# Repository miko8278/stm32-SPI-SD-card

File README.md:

# stm32-SPI-SD-card

This project was developed as part of a Bachelor's thesis for the [BHT Berlin](https://www.bht-berlin.de/) and makes use of the following open-source filesystem implementations:

## FatFs

This project uses **FatFs** by ChaN.

- Project: [FatFs – Official Website](https://elm-chan.org/fsw/ff/00index_e.html)
- The LittleFS source code used by this project is included in this repository under `code/spi-sdcardwrite/FatFs`.

## LittleFS

This project also uses **littlefs** by the littlefs-project.

- Project: [LittleFS – GitHub Repository](https://github.com/littlefs-project/littlefs)
- The littlefs source code used by this project is included in this repository under `code/spi-sdcardwrite/littlefs`.

## Project

The purpose of this project is to investigate and compare filesystem implementations for SD cards operated in SPI mode, using an **STM32G431** microcontroller.

The project is written in **C++20** and developed using **VS Codium**, **Cortex-Debug**, and the **GNU Arm Embedded Toolchain**.

The filesystem implementations are third-party software and are subject to their respective licenses. Please refer to the corresponding license files for the complete license terms.

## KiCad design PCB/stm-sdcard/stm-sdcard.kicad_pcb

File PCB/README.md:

# PCB Page

For this project [KiCAD 10.0](https://www.kicad.org/) was used.

## Used Parts

[ST STM32G431CBT6] https://www.lcsc.com/product-detail/C529355.html
[SD-Card Slot] https://www.lcsc.com/product-detail/C19189036.html
[USB Type-C connector] https://www.lcsc.com/product-detail/C668624.html
[LDO TI] https://www.lcsc.com/product-detail/C15578.html

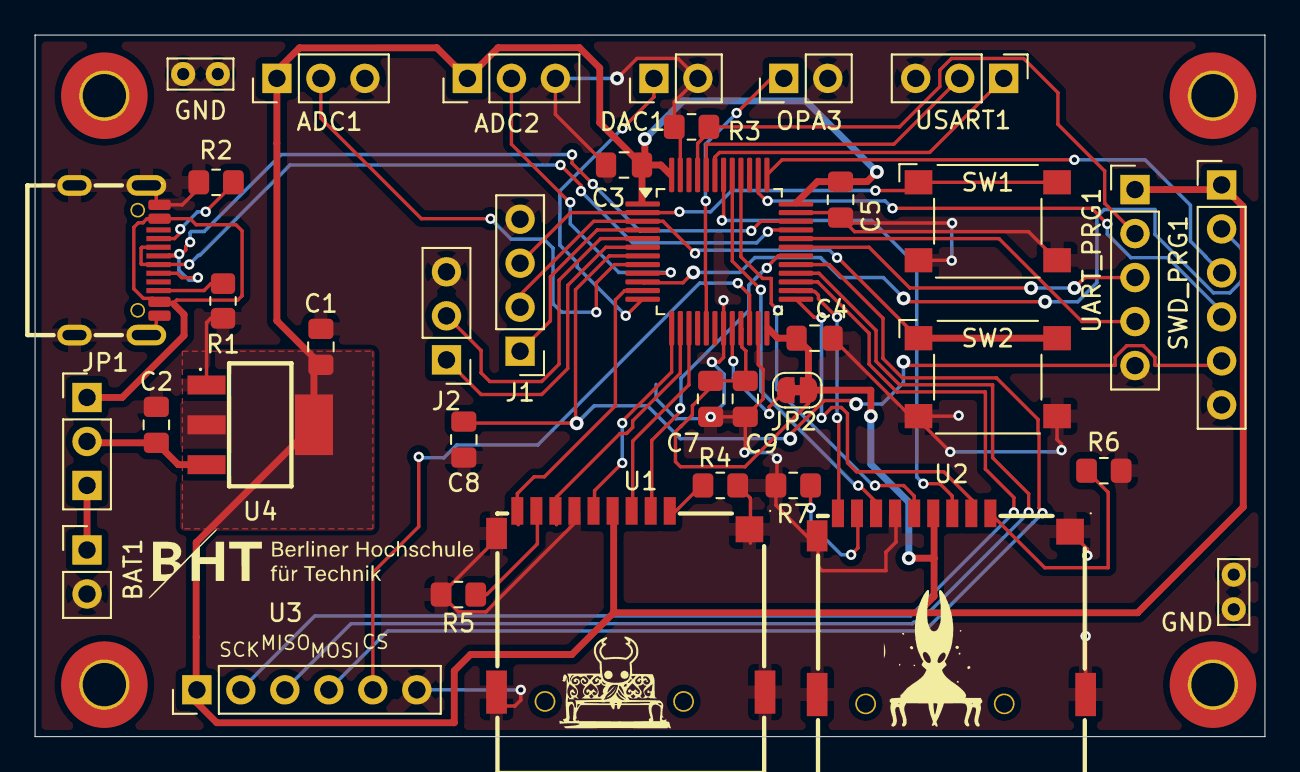
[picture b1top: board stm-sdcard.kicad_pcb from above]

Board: 2 copper layers, 71.0 x 40.5 mm, 37 parts (0 on the bottom side), 46 nets.

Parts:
ADC1, ADC2: Conn_01x03_Pin; PinHeader_1x03_P2.54mm_Vertical
BAT1: Conn_01x02_Pin; PinHeader_1x02_P2.54mm_Vertical
C1: 2.2uF; C_0805_2012Metric_Pad1.18x1.45mm_HandSolder
C2, C9: 1uF; C_0805_2012Metric_Pad1.18x1.45mm_HandSolder
C3, C4, C5, C7, C8: 100nF; C_0805_2012Metric_Pad1.18x1.45mm_HandSolder
DAC1: Conn_01x02_Pin; PinHeader_1x02_P2.54mm_Vertical
GND: TestPoint_Bridge_Pitch2.0mm_Drill0.7mm
GND#2: TestPoint_Bridge_Pitch2.0mm_Drill0.7mm
J1: Conn_01x04_Pin; PinHeader_1x04_P2.54mm_Vertical
J2: Conn_01x03_Pin; PinHeader_1x03_P2.54mm_Vertical
JP1: Jumper_3_Open; PinHeader_1x03_P2.54mm_Vertical
JP2: SolderJumper_2_Bridged; SolderJumper-2_P1.3mm_Bridged_RoundedPad1.0x1.5mm
OPA3: Conn_01x02_Pin; PinHeader_1x02_P2.54mm_Vertical
R1, R2: 5k1; R_0805_2012Metric_Pad1.20x1.40mm_HandSolder
R3: 20K; R_0805_2012Metric_Pad1.20x1.40mm_HandSolder
R4, R5, R6, R7: 50k; R_0805_2012Metric_Pad1.20x1.40mm_HandSolder
STM1: STM32G431CBTx; LQFP-48_7x7mm_P0.5mm
SW1, SW2: SW_Push; SW_SPST_Omron_B3FS-105xP
SWD_PRG1: Conn_01x06_Pin; PinHeader_1x06_P2.54mm_Vertical
U1, U2: HX TF-CARD H1.8; TF-SMD_HX-TF-CARD-H1.8-SY
U3: Conn_01x06_Pin; PinHeader_1x06_P2.54mm_Vertical
U4: TLV1117LV33DCYR; SOT-223_L6.7-W3.5-P2.30-BR
UART_PRG1: Conn_01x05_Pin; PinHeader_1x05_P2.54mm_Vertical
USART1: Conn_01x03_Pin; PinHeader_1x03_P2.54mm_Vertical
USB1: TYPE-C 16P; USB-C-SMD_TYPE-C16PIN_C668624

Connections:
+3.3V: ADC1.1, ADC2.1, C1.1, C3.1, C4.1, C5.1, C7.1, C9.1, JP2.1 (A), STM1.1 (VBAT), STM1.21 (VDDA), STM1.24 (VDD), STM1.36 (VDD), STM1.48 (VDD), SWD_PRG1.1, U1.4 (VDD), U2.4 (VDD), U3.1, U4.2 (OUT), U4.4 (OUT), UART_PRG1.1
+5V: C2.1, JP1.2 (C), U4.3 (IN)
/PA0_ADC1: ADC1.2, STM1.8 (PA0)
/PA1_ADC2: ADC2.2, STM1.9 (PA1)
/PA2_VCP_Tx: STM1.10 (PA2), SWD_PRG1.2
/PA3: STM1.11 (PA3), U1.9 (CD)
/PA4_DAC1: DAC1.1, STM1.12 (PA4)
/PA5: STM1.13 (PA5), U1.5 (CLK)
/PA6: STM1.14 (PA6), U1.7 (DAT0)
/PA7: STM1.15 (PA7), U1.3 (CMD)
/PA8: STM1.30 (PA8), U1.2 (CD/DAT3)
/PA9_Tx_BOOT: STM1.31 (PA9), UART_PRG1.3
/PA10_Rx_BOOT: STM1.32 (PA10), UART_PRG1.4
/PA13_SWDIO: STM1.37 (PA13), SWD_PRG1.3
/PA14_SWDCLK: STM1.38 (PA14), SWD_PRG1.4
/PB1_OPAMP3_OUT: OPA3.1, STM1.17 (PB1)
/PB3: STM1.40 (PB3), U2.5 (CLK)
/PB4: STM1.41 (PB4), U2.7 (DAT0)
/PB5: STM1.42 (PB5), U2.3 (CMD)
/PB6_USART1_RX: STM1.44 (PB7), USART1.2
/PB6_USART1_TX: STM1.43 (PB6), USART1.1
/PB8_BOOT0: R3.2, STM1.45 (PB8), UART_PRG1.2
/PB10: STM1.22 (PB10), U3.5
/PB11: STM1.25 (PB11), U2.2 (CD/DAT3)
/PB12: STM1.26 (PB12), U2.9 (CD)
/PB13: STM1.27 (PB13), U3.2
/PB14: STM1.28 (PB14), U3.3
/PB15: STM1.29 (PB15), U3.4
/PC13: J1.3, STM1.2 (PC13), SW1.1
/PC14: J1.2, STM1.3 (PC14), SW2.1
/PC15: J1.1, STM1.4 (PC15)
/PF0: J2.2, STM1.5 (PF0)
/PF1: J2.1, STM1.6 (PF1)
/PG10_nRST: C8.2, STM1.7 (PG10), SWD_PRG1.5
/SPI-SDcard/PULLUP1: R4.1, U1.1 (DAT2)
/SPI-SDcard/PULLUP2: R5.1, U1.8 (DAT1)
/SPI-SDcard/PULLUP3: R6.1, U2.1 (DAT2)
/SPI-SDcard/PULLUP4: R7.1, U2.8 (DAT1)
/USB_D+: STM1.34 (PA12), USB1.A6 (DP1), USB1.B6 (DP2)
/USB_D-: STM1.33 (PA11), USB1.A7 (DN1), USB1.B7 (DN2)
/USB_VBUS: JP1.1 (A), USB1.A4B9 (VBUS), USB1.B4A9 (VBUS)
/U_BAT: BAT1.1, JP1.3 (B)
GND: ADC1.3, ADC2.3, BAT1.2, C1.2, C2.2, C3.2, C4.2, C5.2, C7.2, C8.1, C9.2, DAC1.2, GND.1, GND#2.1, J1.4, J2.3, OPA3.2, R1.2, R2.2, R3.1, R4.2, R5.2, R6.2, R7.2, STM1.19 (VSSA), STM1.23 (VSS), STM1.35 (VSS), STM1.47 (VSS), SW1.2, SW2.2, SWD_PRG1.6, U1.6 (VSS), U1.10 (GND), U1.11 (GND), U1.12 (GND), U1.13 (GND), U2.6 (VSS), U2.10 (GND), U2.11 (GND), U2.12 (GND), U2.13 (GND), U3.6, U4.1 (ADJ/GND), UART_PRG1.5, USART1.3, USB1.1 (SHELL), USB1.2 (SHELL), USB1.3 (SHELL), USB1.4 (SHELL), USB1.A1B12 (GND), USB1.B1A12 (GND)
unnamed: JP2.2 (B), STM1.20 (VREF+)
unnamed: R2.1, USB1.A5 (CC1)
unnamed: R1.1, USB1.B5 (CC2)
